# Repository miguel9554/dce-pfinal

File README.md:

# repositorio del proyecto final de dce - 1c2019

integrantes:

- Juan Ciafardini, 97921
- Miguel Perez Andrade, 98599
- Luis Tomás Quiroga, 96337

# 19/12/2019

## 18:00, primera medición

Medimos el punto de operación del amplificador diferencial y la fuente de corriente

* V_R10 [mV]:   571.2
* V_R8  [mV]:   383.8 
* V_R7  [mV]:   5.2
* V_R6  [mV]:   377.7
* V_R2  [mV]:   99
* V_R1  [mV]:   57.3
* V_bQ2 [mV]:   631
* V_bQ3 [mV]:   202.1

Problemas:

* Falta una vía en el emisor de Q2          -> corregido
* Un cacho de tierra no está conectado      -> conecta nada más las resistencias de la etapa de potencia, después lo conectamos
* Se rompio el contacto del capa C3         -> arreglar cuando se mida la señal

## 19:28, segunda medición

Medimos el punto de operación del amplificador diferencial y la fuente de corriente

* V_R10 [mV]:   568.1
* V_R8  [mV]:   380.7 
* V_R7  [mV]:   5.2
* V_R6  [mV]:   374.5
* V_R2  [mV]:   98.1
* V_R1  [mV]:   156.4
* V_bQ2 [mV]:   628
* V_eQ2 [V]:    -9.97
* V_bQ3 [mV]:   200.1
* V_eQ3  [V]:   -9.29

Cálculos

* I_R7  :   0.052u
* I_R6  :   3.74m
* I_R2  :   1.44m
* I_R1  :   2.3m
* I_R15 :   52u
* I_R5  :   16.67u

# 03/02/2020

## 16:40, 1ra medición

Medimos el punto de operación del amplificador diferencial y la fuente de corriente (nodos diff LT)

* V_R10 [mV]:   573.2           (J9 vs V+)
* V_R8  [mV]:   387.5           (J4 vs V+)
* V_R7  [mV]:   5.3         (entre J19 y J2)
* V_R6  [mV]:   378.4           (entre J19 y J20)
* V_R2  [mV]:   99.8            (J3 vs V-)
* V_R1  [mV]:   157.2           (J6 vs V-, entrada)
* V_bQ2 [mV]:   604.7           (J15)
* V_eQ2 [V]:    1.175
* V_bQ3 [mV]:   200.8
* V_eQ3  [V]:   0.806

Soldamos los conectores de Q2 y Q4 que estaban desconectados, medimos de vuelta

## 17:37, 2da medición

Medimos el punto de operación del amplificador diferencial y la fuente de corriente (nodos diff LT)

* V_R10 [mV]:   571.1               (J9 vs V+)
* V_R8  [mV]:   383.5               (J4 vs V+)
* V_R7  [mV]:   190.8               (entre J19 y J2)
* V_R6  [mV]:   191.1               (entre J19 y J20)
* V_R2  [mV]:   130.9               (J3 vs V-)
* V_R1  [mV]:   129.0               (J6 vs V-, entrada)
* V_bQ2 [mV]:   102.3               (J15)
* V_eQ2 [mV]:   696.0
* V_bQ3 [mV]:   103.0
* V_eQ3 [mV]:   696.0

Soldamos R10 a V+, y el capa de filtrado de la fuente de corriente (C7 en Kicad) a V+

## 18:32, 3ra medición

Medimos el punto de operación del amplificador diferencial y la fuente de corriente (nodos diff LT)

* V_R10 [mV]:   563.5               (J9 vs V+)
* V_R8  [mV]:   538.5               (J4 vs V+)
* V_R7  [mV]:   267.4               (entre J19 y J2)
* V_R6  [mV]:   267.3               (entre J19 y J20)
* V_R2  [mV]:   183.0               (J3 vs V-)
* V_R1  [mV]:   180.0               (J6 vs V-, entrada)
* V_bQ2 [mV]:   141.8               (J15)
* V_eQ2 [mV]:   742.0
* V_bQ3 [mV]:   143.2
* V_eQ3 [mV]:   742.0

Cambiamos la resistencia R8 por una de 47, era de 100 y estaba dando mal por eso

## 19:14, 4ta medición

Medimos el punto de operación del amplificador diferencial y la fuente de corriente (nodos diff LT)

* V_R10 [mV]:   561.6               (J9 vs V+)
* V_R8  [mV]:   497.8               (J4 vs V+)
* V_R7  [mV]:   528.9               (entre J19 y J2)
* V_R6  [mV]:   529.4               (entre J19 y J20)
* V_R2  [mV]:   361.8               (J3 vs V-)
* V_R1  [mV]:   357.5               (J6 vs V-, entrada)
* V_bQ2 [mV]:   274.3               (J15)
* V_eQ2 [mV]:   880.0
* V_bQ3 [mV]:   275.5
* V_eQ3 [mV]:   879.0

Medimos con 30V GUARDA CON LAS CHISPAS

## 19:21, 5ta medición

Medimos el punto de operación del amplificador diferencial y la fuente de corriente (nodos diff LT)

* V_R10 [mV]:   582.7               (J9 vs V+)
* V_R8  [mV]:   548.5               (J4 vs V+)
* V_R7  [mV]:   583.3               (entre J19 y J2)
* V_R6  [mV]:   581.7               (entre J19 y J20)
* V_R2  [mV]:   399.1               (J3 vs V-)
* V_R1  [mV]:   392.9               (J6 vs V-, entrada)
* V_bQ2 [mV]:   245.1               (J15)
* V_eQ2 [mV]:   795.0
* V_bQ3 [mV]:   245.7
* V_eQ3 [mV]:   796.0

# 04/02/2020

## 17:42, 1ra medición

Medimos después de soldar el vas sin conectarlo todavía, para ver que todo siga andando

* V_R10 [mV]:   564.2           (J9 vs V+)
* V_R8  [mV]:   497.2           (J4 vs V+)
* V_R7  [mV]:   527.4           (entre J19 y J2)
* V_R6  [mV]:   527.1           (entre J19 y J20)
* V_R2  [mV]:   360.7           (J3 vs V-)
* V_R1  [mV]:   356.0           (J6 vs V-, entrada)
* V_bQ2 [mV]:   274.0           (J15)
* V_eQ2 [mV]:   883.0
* V_bQ3 [mV]:   276.3
* V_eQ3 [mV]:   883.0

## 18:00, 2da medición

Medimos con todo conectado (vas)

* V_R10 [mV]:   32          (J9 vs V+)
* V_R8  [mV]:   58.9            (J4 vs V+)
* V_R7  [mV]:   93.9        (entre J19 y J2)
* V_R6  [mV]:   30.4            (entre J19 y J20)
* V_R2  [mV]:   21.8            (J3 vs V-)
* V_R1  [mV]:   20.3            (J6 vs V-, entrada)
* V_bQ2 [mV]:   7670            (J15)
* V_eQ2 [mV]:   8390
* V_bQ3 [mV]:   7860
* V_eQ3 [mV]:   8460
* V_Vas [mv]:   7980

## 18:26, 3ra medición

Arreglamos la pista que se había cortado (la que iba entre la salida del vas y el diodo) y dimos vuelta los diodos

* V_R10 [mV]:   32          (J9 vs V+)
* V_R8  [mV]:   58.9            (J4 vs V+)
* V_R7  [mV]:   93.9        (entre J19 y J2)
* V_R6  [mV]:   30.4            (entre J19 y J20)
* V_R2  [mV]:   21.8            (J3 vs V-)
* V_R1  [mV]:   20.3            (J6 vs V-, entrada)
* V_bQ2 [mV]:   7670            (J15)
* V_eQ2 [mV]:   8390
* V_bQ3 [mV]:   7860
* V_eQ3 [mV]:   8460
* V_Vas [mv]:   7980

## 19:09, 4ta medición

No estaba conectado el jumper que conectaba la salida del diferencial con el buffer, lo soldamos. También soldamos una pata del transitor del mult de vbe.

* Vcc   [V]:    10   |  30
* V_R10 [mV]:   560.2|580.0             (J9 vs V+)
* V_R8  [mV]:   502.9|567.0             (J4 vs V+)
* V_R7  [mV]:   534.4|602.0             (entre J19 y J2)
* V_R6  [mV]:   536.3|607.5             (entre J19 y J20)
* V_R2  [mV]:   367.1|413.2             (J3 vs V-)
* V_R1  [mV]:   364.9|411.3             (J6 vs V-, entrada)
* V_bQ2 [mV]:   273.6|248.3             (J15)
* V_eQ2 [mV]:   879.0|794.0
* V_bQ3 [mV]:   268.4|237.7
* V_eQ3 [mV]:   875.0|790.0
* V_Vas [mv]:   016.0|019.0

# 06/02/2020

## 17:21, 1ra medición

Alimentación de 27.6 V

* V_R10 [mV]:   590.8           (J9 vs V+)
* V_R8  [mV]:   599.0           (J4 vs V+)
* V_R7  [mV]:   124.3           (entre J19 y J2)
* V_R6  [mV]:   1042.0          (entre J19 y J20)
* V_R2  [mV]:   446.0           (J3 vs V-)
* V_R1  [mV]:   524.0           (J6 vs V-, entrada)
* V_bQ2 [mV]:   15023.0         (J15)
* V_eQ2 [mV]:   24040.0
* V_bQ3 [mV]:   22038.0
* V_eQ3 [mV]:   23075.0

## 18:23, 2da medición

Medición con la realimentación conectada, no está funcionando

* V_R10 [mV]:   603.5           (J9 vs V+)
* V_R8  [mV]:   600.0           (J4 vs V+)
* V_R7  [mV]:   126.2           (entre J19 y J2)
* V_R6  [mV]:   1430.0          (entre J19 y J20)
* V_R2  [mV]:   448.0           (J3 vs V-)
* V_R1  [mV]:   530.0           (J6 vs V-, entrada)
* V_bQ2 [mV]:   15300.0         (J15)
* V_eQ2 [mV]:   24640.0
* V_bQ3 [mV]:   22440.0
* V_eQ3 [mV]:   24000.0

## 18:31, 3ra medición

Medición solo del diferencial

* V_R10 [mV]:   600.8           (J9 vs V+)
* V_R8  [mV]:   558.0           (J4 vs V+)
* V_R7  [mV]:   569.5           (entre J19 y J2)
* V_R6  [mV]:   617.0           (entre J19 y J20)
* V_R2  [mV]:   404.6           (J3 vs V-)
* V_R1  [mV]:   411.0           (J6 vs V-, entrada)
* V_bQ2 [mV]:   332.0           (J15)
* V_eQ2 [mV]:   898.7
* V_bQ3 [mV]:   281.0
* V_eQ3 [mV]:   846.0

# 10/02/2020

# 16:29, 1ra medición

Como no anduvo una mierda la semana pasada, vamos a medir todos los transistores para ver si alguno está roto. Nos basamos en lo explicado en https://www.fluke.com/en-us/learn/best-practices/test-tools-basics/digital-multimeters/how-to-test-diodes-using-a-digital-multimeter y https://electronics.stackexchange.com/a/83752. Los nombres de los transistores van a estar referidos al esquemático de kicad. Todas las mediciones se hacen con un multimetro en modo diodo

* Q3
    * VbeD [mv]: 646
    * VbeI [mv]: 1800
    * VbcD [mv]: 641
    * VbcI [mv]: 0L
    * Vec [mv]: 0L
    * Vce [mv]: 1343
* Q1
    * VbeD [mv]: 649
    * VbeI [mv]: 0L
    * VbcD [mv]: 645
    * VbcI [mv]: 0L
    * Vec [mv]: 700
    * Vce [mv]: 0L
* Q5
    * VbeD [mv]: 642
    * VbeI [mv]: 0L
    * VbcD [mv]: 639
    * VbcI [mv]: 0L
    * Vec [mv]: 0L
    * Vce [mv]: 0L
* Q2
    * VbeD [mv]: 649
    * VbeI [mv]: 0L
    * VbcD [mv]: 648
    * VbcI [mv]: 0L
    * Vec [mv]: 0L
    * Vce [mv]: 1300

* Q2 (tiene cortado base y colector)
    * VbeD [mv]: 600
    * VbeI [mv]: 0L
    * VbcD [mv]: -
    * VbcI [mv]: -
    * Vec [mv]: -
    * Vce [mv]: -

* Q7
    * VbeD [mv]: 656
    * VbeI [mv]: 0L
    * VbcD [mv]: 651
    * VbcI [mv]: 0L
    * Vec [mv]: 710
    * Vce [mv]: 710

* Q10
    * VbeD [mv]: 655
    * VbeI [mv]: 1415
    * VbcD [mv]: 652
    * VbcI [mv]: 0L
    * Vec [mv]: 911
    * Vce [mv]: 0L

* Q8
    * VbeD [mv]: 645
    * VbeI [mv]: 844
    * VbcD [mv]: 640
    * VbcI [mv]: 0L
    * Vec [mv]: 861
    * Vce [mv]: 1715

* Q6
    * VbeD [mv]: 1403
    * VbeI [mv]: 1430
    * VbcD [mv]: 1722
    * VbcI [mv]: 1723
    * Vec [mv]: 700
    * Vce [mv]: 888

* Q9
    * VbeD [mv]: 589
    * VbeI [mv]: 1040
    * VbcD [mv]: 583
    * VbcI [mv]: 1695
    * Vec [mv]: 1008
    * Vce [mv]: 1799

Medimos un mje340 y un mpsa06 buenos, sin usar

* MJE340
    * VbeD [mv]: 618
    * VbeI [mv]: 0L
    * VbcD [mv]: 613
    * VbcI [mv]: 0L
    * Vec [mv]: 0L
    * Vce [mv]: 0L

* MPSA06
    * VbeD [mv]: 668
    * VbeI [mv]: 0L
    * VbcD [mv]: 665
    * VbcI [mv]: 0L
    * Vec [mv]: 0L
    * Vce [mv]: 0L

Con estás ultimas mediciones, parece que están todos rotos salvo Q5. Es posible que el circuito externo que tiene cada dispositivo esté alterando las mediciones, y los resultados no sean correctos. Vamos a sacar los transistores y medirlos solos para comprobar.

Mediciones con los transistores desoldados:

* Q9
    * VbeD [mv]: 624
    * VbeI [mv]: 0L
    * VbcD [mv]: 620
    * VbcI [mv]: 0L
    * Vec [mv]: 0L
    * Vce [mv]: 0L

* Q3
    * VbeD [mv]: 646
    * VbeI [mv]: 0L
    * VbcD [mv]: 643
    * VbcI [mv]: 0L
    * Vec [mv]: 0L
    * Vce [mv]: 0L

* Q10
    * VbeD [mv]: 661
    * VbeI [mv]: 0L
    * VbcD [mv]: 630
    * VbcI [mv]: 0L
    * Vec [mv]: 0L
    * Vce [mv]: 0L

* Q7 (parece estar cagado, ver la potencia)
    * VbeD [mv]: 653
    * VbeI [mv]: 0L
    * VbcD [mv]: 650
    * VbcI [mv]: 0L
    * Vec [mv]: \~710
    * Vce [mv]: \~710

Con Q9 comprobamos la medición volviendo a soldarlo, y dio mal igual que antes. Esto nos da la pauta de que el circuito externo a cada dispositivo esta perturbando la medición cuando medimos al dispositivo conectado al resto del circuito.

Q7 parece estar cagado, la medición del transistor solo da mal (no hay abierto entre colector y emisor). En base a esto y a que el circuito diferencial estaba funcionando sin la etapa VAS, suponemos que cambiar este transistor va a solucionar el problema.

## 18:52, 2da medición

Medimos con Q7 reemplazado, el circuito diferencial con el vas (medimos rápidamente la fuente de corriente y el diferencial antes de esto y daba bien)
Se quemó la resistencia R4 (en PCB)

* V_R10 [mV]:   573.3           (J9 vs V+)
* V_R8  [mV]:   536.6           (J4 vs V+)
* V_R7  [mV]:   081.5           (entre J19 y J2)
* V_R6  [mV]:   1018.0           (entre J19 y J20)
* V_R2  [mV]:   384.0           (J3 vs V-)
* V_R1  [mV]:   430.5           (J6 vs V-, entrada)
* V_bQ2 [mV]:   -15150          (J15)
* V_eQ2 [mV]:   -18160
* V_bQ3 [mV]:   -14260
* V_eQ3 [mV]:   -19320
* V_oVAS[mV]:   -18750

## 19:07, 2da medición

Medimos solo el diferencial para comprobar que siga andando

* V_R10 [mV]:   599.0           (J9 vs V+)
* V_R8  [mV]:   541.9           (J4 vs V+)
* V_R7  [mV]:   530.8           (entre J19 y J2)
* V_R6  [mV]:   577.9           (entre J19 y J20)
* V_R2  [mV]:   373.6           (J3 vs V-)
* V_R1  [mV]:   378.4           (J6 vs V-, entrada)
* V_bQ2 [mV]:   319.7          (J15)
* V_eQ2 [mV]:   886.6
* V_bQ3 [mV]:   270.4
* V_eQ3 [mV]:   843.4

Vamos a medir los transistores del par diferencial y su carga activa

* Q1
    * VbeD [mv]: 647
    * VbeI [mv]: 0L
    * VbcD [mv]: 643.8
    * VbcI [mv]: 0L
    * Vec [mv]: 0L
    * Vce [mv]: 0L

* Q5
    * VbeD [mv]: 640.0
    * VbeI [mv]: 0L
    * VbcD [mv]: 643.4
    * VbcI [mv]: 0L
    * Vec [mv]: 0L
    * Vce [mv]: 0L

* Q2
    * VbeD [mv]: 668.0
    * VbeI [mv]: 0L
    * VbcD [mv]: 599.5
    * VbcI [mv]: 0L
    * Vec [mv]: 0L
    * Vce [mv]: 0L

* Q4
    * VbeD [mv]: 600.0
    * VbeI [mv]: 0L
    * VbcD [mv]: 666.0
    * VbcI [mv]: 0L
    * Vec [mv]: 0L
    * Vce [mv]: 0L

* Q6
    * VbeD [mv]: 582.5
    * VbeI [mv]: 0L
    * VbcD [mv]: 643.5
    * VbcI [mv]: 0L
    * Vec [mv]: 0L
    * Vce [mv]: 0L

* Q8
    * VbeD [mv]: 642.5
    * VbeI [mv]: 0L
    * VbcD [mv]: 640.0
    * VbcI [mv]: 0L
    * Vec [mv]: 0L
    * Vce [mv]: 0L

##  20:06, 3ra medición

Probamos todos los transistores y parecen estar bien. Soldamos la pistas de la base de Q2 y el colector Q6 (fuente de corriente) que no estaban unidas. Medimos de vuelta

* V_R10 [mV]:   571.5           (J9 vs V+)
* V_R8  [mV]:   558           (J4 vs V+)
* V_R7  [mV]:   85.8           (entre J19 y J2)
* V_R6  [mV]:   10892           (entre J19 y J20)
* V_R2  [mV]:   411.4           (J3 vs V-)
* V_R1  [mV]:   460           (J6 vs V-, entrada)
* V_bQ2 [mV]:   -1513          (J15)
* V_eQ2 [mV]:   -18.33
* V_bQ3 [mV]:   -14092
* V_eQ3 [mV]:   -19.53
* V_oVAS[mV]:   -18507

Las fuentes daban 30 mili cada una
Medimos el diferencial primero y estaba balanceado

#   11/02/2020

##  18:16, 1ra medición

Medición sin realizar ningún cambio.

* V_R10 [mV]:   603.4           (J9 vs V+)
* V_R8  [mV]:   564.0           (J4 vs V+)
* V_R7  [mV]:   576.7           (entre J19 y J2)
* V_R6  [mV]:   581.8           (entre J19 y J20)
* V_R2  [mV]:   395.5           (J3 vs V-)
* V_R1  [mV]:   393.8           (J6 vs V-, entrada)
* V_bQ2 [mV]:   359.7          (J15)
* V_eQ2 [mV]:   938.0
* V_bQ3 [mV]:   359.2
* V_eQ3 [mV]:   932.0
* V_oVAS[mV]:   075.4

El problema era el potenciómetro del multiplicador de vbe que estaba flojo.

##  Modificaciones
* Sacamos el capacitor de 1uF entre -VCC y GND porque estaba cortada la pista de -VCC en ese nodo.
* Cambiamos el potenciómetro, pareciera seguir habiendo algún problema relacionado a su conexión.

# 13/02/2020

Empezamos viendo si el pote está bien soldado, si hay la resistencia que tiene que haber entre las pistas. Lo resoldamos y parece dar bien

##  16:55, 1ra medición

Medición después de soldar bien el pote.

* V_R10 [mV]:   605.7           (J9 vs V+)
* V_R8  [mV]:   569.1           (J4 vs V+)
* V_R7  [mV]:   580.5           (entre J19 y J2)
* V_R6  [mV]:   585.9           (entre J19 y J20)
* V_R2  [mV]:   397.3           (J3 vs V-)
* V_R1  [mV]:   396.0           (J6 vs V-, entrada)
* V_bQ2 [mV]:   367.4          (J15)
* V_eQ2 [mV]:   946.0
* V_bQ3 [mV]:   365.9
* V_eQ3 [mV]:   941.0
* V_oVAS[mV]:   57.0

Da bien! Parece ser que el problema era el pote.

Ahora vamos a medir la ganancia con fin=1k.
Vpp entrada [mV]    Vpp salida [V]  Ganancia
200     5.4     27
300     8.48    28.26
400     11.12   27.8
500     13.8    27.6
600     16.20   27
800     21.2    26.5
1000    26.40   26.4
1200    31.8    26.5
1500    39.20   26.13
1530    40      26.14

Ahora vamos a medir la ganancia con fin=10k (hay que recalcular la ganancia).
Vpp entrada [mV]    Vpp salida [V]  Ganancia
200     5.12    27
300     8.48    28.26
400     11.04   27.8
500     13.44   27.6
600     16.00   27
800     21.2    26.5
1000    26.40   26.4
1200    31.8    26.5
1500    40      26.13
1530    40      26.14

Medimos la salida con 1 Vpp a la entrada, y variando la frecuencia.
f [Hz]  Vpp salida [V]
20  26.8
200 26.8
2k  26.6
20k 26.8
50k 26.8
200k    26

Da joya la baja potencia, arrancamos a soldar la parte de potencia.

Cosas que hay que comprar:
* Disipadores
* Pasta térmica
* Diodos 1N4148
* Capacitores de 1u y 50V
* Resistencia de 50W

Cosas para ver:
* Ver porque que en el esquemático hay 1N4148 cuando debería haber LM385
* Soldar todas las pistas de los componentes de potencia cuando 
* Cambiar C7 que está quemado, y volver a poner C8

# 17/02/2020

La idea de hoy era soldar toda la etapa de potencia y montar los disipadores. El disipador de los transistores de potencia y el multiplicador de vbe no se pudo montar, asi que solo soldamos la etapa de potencia. Medimos continuidad y parece estar todo bien conectado. Solo falta soldar las pistas de arriba de los transistores que van al disipador. No lo hicimos para que tengan mas movilidad cuando pongamos el disipador. Mañana hay que comprar
* Disipador ZD27-10, de 10 cm de largo
* Tornillos y mica

# 21/02/2020

Ya está todo soldado y armado, vamos a medir la polarización para todo el circuito

## 1ra medición, 18:26

* V_R10 [mV]:   603
* V_R8  [mV]:   572
* V_R7  [mV]:   579.5
* V_R6  [mV]:   581.7
* V_R2  [mV]:
* V_R1  [mV]:
* V_bQ2 [mV]:
* V_eQ2 [mV]:
* V_bQ3 [mV]:
* V_eQ3 [mV]:
* V_oVAS[mV]:
* V_bQ11[mV]:
* V_bQ16[mV]:
* V_bQ12[mV]:
* V_bQ15[mV]:
* V_R18 [mV]:
* V_R19 [mV]:

Tratabamos de medir y cuando mediamos algunos nodos (VoVas, VR7, VR6) la fuente empezaba a entregar corrientes erróneas. Vamos a medir con un osciloscopio enganchado en VoVas para ver si hay oscilaciones

Encontramos una oscilación, chequeamos en la simulación y encontramos que con el capa de compensación de 100p, el circuito está inestable. Lo reemplazamos por uno de 470p que da estable. REEMPLAZAR EN EL LTSPICE EL CAPA DE 100P POR ESTE DE 470P

Hablamos con Fede
- Tratar de que haya aprox 100 mA en la rama de salida, ahora hay 500mA. Probamos llevando la resistencia del mult de vbe 1.5K, daba bien la THD y aprox 100 mA a la salida, ver si cambiamos el pote por uno de 500.
- SIEMPRE limitar la corriente de las fuentes antes de medir. Para esto, llevar a cero la tensión y el límite de corriente, cortocircuitar la fuente e incrementar el límite de corriente hasta llegar a la limitación deseada.

Cosas para cambiar en las simulaciones
- Poner un capacitor de 470p
- Ver la resistencia del mult de vbe, en 1.5k aparentemente da bien

## 2da medición, 19:58

Medimos después de reemmplazar el capa de 100p por uno de 470p

* V_R10 [mV]:   610
* V_R8  [mV]:   567
* V_R7  [mV]:   577
* V_R6  [mV]:   584
* V_R2  [mV]:   397.4
* V_R1  [mV]:   396.9
* V_bQ2 [mV]:   370.2
* V_eQ2 [mV]:   954
* V_bQ3 [mV]:   369.2
* V_eQ3 [mV]:   948
* V_oVAS[mV]:   -1914

# 28/02/20

Vamos a medir la polarización de la etapa de potencia

## 1ra medición, 19:54

Medimos 

* V_R10 [mV]: 599 
* V_R8  [mV]: 568
* V_R7  [mV]: 539
* V_R6  [mV]: 583
* V_R2  [mV]: 396
* V_R1  [mV]: 394
* V_bQ2 [mV]: 356
* V_eQ2 [mV]: 930
* V_bQ3 [mV]: 356
* V_eQ3 [mV]: 926
* V_oVAS[mV]: -1800
* V_bQ11[mV]: 1060
* V_bQ16[mV]: 984
* V_R20 [mV]: 848
* V_R18 [mV]: 0
* V_R19 [mV]: 0
* V_o   [mV]: 57

## 2da medición, 20:25

Soldamos el pin de alimentación de V+, estaba desconectado. Medimos y NO DABA, no medimos todos los nodos por paja

* V_R10 [mV]: 
* V_R8  [mV]: 
* V_R7  [mV]: 
* V_R6  [mV]: 583
* V_R2  [mV]: 396
* V_R1  [mV]: 394
* V_bQ2 [mV]: 356
* V_eQ2 [mV]: 930
* V_bQ3 [mV]: 356
* V_eQ3 [mV]: 926
* V_oVAS[mV]: -1800
* V_bQ11[mV]: 1060
* V_bQ16[mV]: 984
* V_R20 [mV]: 848
* V_R18 [mV]: 0
* V_R19 [mV]: 
* V_o   [mV]: 56

## 3ra medición, 20:50

Soldamos bien el colector de Q17 que no estaba haciendo contacto con la pista. NO DIO

## 4ta medición, 21:08

Soldamos bien el emisor de Q18 que no estaba haciendo contacto con la resistencia R22.

driver arriba
23.96
24.4

driver abajo
24.03
24.4

transistor exterior arriba
9.99
10.2

Vimos que llevando el pote a 0, teníamos 0.05mV sobre las resistencias de emisor, y si lo tirabamos a 200, había 0V. Hay que bajar la resistencia.

# 02/03/202

Modificamos la resistencia del multiplicador de vbe a 1.2 k más el preset. Procedemos a medir la polarización.

# Primera medición, 14:55

Sin conectar las fuentes internas

* V_R10 [mV]: 612             (J9 vs V+)
* V_R8  [mV]: 572             (J4 vs V+)
* V_R7  [mV]: 587             (entre J19 y J2)
* V_R6  [mV]: 589             (entre J19 y J20)
* V_R2  [mV]: 403             (J3 vs V-)
* V_R1  [mV]: 402             (J6 vs V-, entrada)
* V_bQ2 [mV]: 361            (J15)
* V_eQ2 [mV]: 938  
* V_bQ3 [mV]: 360  
* V_eQ3 [mV]: 934  
* V_oVAS[mV]: -1980
* V_bQ11[mV]: 
* V_bQ16[mV]: 
* V_R20 [mV]: 
* V_R18 [mV]: 
* V_R19 [mV]: 
* V_o   [mV]: 57

Corriente de las fuentes entre 40 y 50 mA.

# Segunda medición, 15:30

Conectadas las fuentes internas

* V_R10 [mV]: 601             (J9 vs V+)
* V_R8  [mV]: 576             (J4 vs V+)
* V_R7  [mV]: 584             (entre J19 y J2)
* V_R6  [mV]: 588             (entre J19 y J5)
* V_R2  [mV]: 400             (J3 vs V-)
* V_R1  [mV]: 398             (J6 vs V-, entrada)
* V_bQ2 [mV]: 354            (J15)
* V_eQ2 [mV]: 926  
* V_bQ3 [mV]: 352  
* V_eQ3 [mV]: 923  
* V_oVAS[mV]: -2000
* V_bQ11[mV]: 1192
* V_bQ16[mV]: 1295
* V_R20 [mV]: 1278
* V_R18 [mV]: 5				(50 mA)
* V_R19 [mV]: 5
* V_o   [mV]: 55

# Tercera medición, 15:56

Cambiamos la resistencia del preset de 40 ohm a 120 ohm para bajar la corrien te en la rama de salida.

* V_R10 [mV]: 605
* V_R8  [mV]: 574
* V_R7  [mV]: 585
* V_R6  [mV]: 590
* V_R2  [mV]: 401
* V_R1  [mV]: 399
* V_bQ2 [mV]: 356
* V_eQ2 [mV]: 931 
* V_bQ3 [mV]: 356  
* V_eQ3 [mV]: 926
* V_oVAS[mV]: -1970
* V_bQ11[mV]: 1249
* V_bQ16[mV]: 1140
* V_R20 [mV]: 1278
* V_R18 [mV]: 0.92				(9.2 mA)
* V_R19 [mV]: 0.92
* V_o   [mV]: 52

# Cuarta medición, 17:13

Se produjo un corto al medir señal.

* V_R10 [mV]: 608
* V_R8  [mV]: 573
* V_R7  [mV]: 585
* V_R6  [mV]: 590
* V_R2  [mV]: 401
* V_R1  [mV]: 399
* V_bQ2 [mV]: 362
* V_eQ2 [mV]: 946 
* V_bQ3 [mV]: 362  
* V_eQ3 [mV]: 940
* V_oVAS[mV]: -1950
* V_bQ11[mV]: 1290
* V_bQ16[mV]: 1129
* V_R20 [mV]: 1190
* V_R18 [mV]: 0.27				(2.5 mA)
* V_R19 [mV]: 0.25
* V_o   [mV]: 54

Bajó la corriente de salida. Probablemente se corrió el potenciómetro.
Se solucionó acomodando algunos contactos de las fuentes de alimentación.

El circuito presenta una senoidal de 7.6 MHz y 1.2 Vpp a la salida en ausencia
de señal de entrada. Al agregarse la señal de entrada se suma a la salida con poca amplificación.
Probar cambiar capacitor de compensación.

# 03/03/202

Soldamos dos capacitores de 220 pF entre base y colector de los transistores externos del driver.

# Primera medición, 16:23

* V_R10 [mV]: 604
* V_R8  [mV]: 570
* V_R7  [mV]: 581
* V_R6  [mV]: 587
* V_R2  [mV]: 399
* V_R1  [mV]: 397
* V_bQ2 [mV]: 355
* V_eQ2 [mV]: 932  
* V_bQ3 [mV]: 353 
* V_eQ3 [mV]: 928  
* V_oVAS[mV]: -1980
* V_bQ11[mV]: 1249
* V_bQ16[mV]: 1146
* V_R20 [mV]: 1190
* V_R18 [mV]: 0.90		(9 mA)
* V_R19 [mV]: 0.93
* V_o   [mV]: 48

La ganancia está muy afectada para casi todas las frecuencias, ya en la salida del VAS.
La mayor ganancia encontrada es 3, para 1 MHz.
La cuadrada muestra que no està sobrecompensado.

# 05/03/2020

Medimos primero sin cambiar nada

* V_R10 [mV]: 601
* V_R8  [mV]: 574
* V_R7  [mV]: 584
* V_R6  [mV]: 587
* V_R2  [mV]: 400
* V_R1  [mV]: 399
* V_bQ2 [mV]: 350
* V_eQ2 [mV]: 924  
* V_bQ3 [mV]: 350 
* V_eQ3 [mV]: 919  
* V_oVAS[mV]: -1936
* V_bQ11[mV]: 1277
* V_bQ16[mV]: 1104
* V_R20 [mV]: 1177
* V_R18 [mV]: 0.80      (8 mA)
* V_R19 [mV]: 0.90
* V_o   [mV]: 48

Medimos para verificar que esté igual que al inicio

* V_R10 [mV]: 600
* V_R8  [mV]: 571
* V_R7  [mV]: 582
* V_R6  [mV]: 587
* V_R2  [mV]: 398
* V_R1  [mV]: 397
* V_bQ2 [mV]: 345
* V_eQ2 [mV]: 919  
* V_bQ3 [mV]: 346 
* V_eQ3 [mV]: 913  
* V_oVAS[mV]: -1968
* V_bQ11[mV]: 1241
* V_bQ16[mV]: 1137
* V_R20 [mV]: 1181
* V_R18 [mV]: 1.80      (18 mA)
* V_R19 [mV]: 1.70
* V_o   [mV]: 45

Si se toca con metal Vin, Vout, R18 o R19, VbQ2: aparece la oscilación de 7 Mhz 2 Vpp a la salida.
Si se toca VbQ3: la tensión aumenta indefinidamente en amplitud (a veces).

# 06/03/2020

Medimos después de agergar un capa de 220 pF en paralelo con el que ya pusimos en Q12

* V_R10 [mV]: 602
* V_R8  [mV]: 573
* V_R7  [mV]: 584
* V_R6  [mV]: 587
* V_R2  [mV]: 399
* V_R1  [mV]: 397
* V_bQ2 [mV]: 366
* V_eQ2 [mV]: 957  
* V_bQ3 [mV]: 362 
* V_eQ3 [mV]: 953  
* V_oVAS[mV]: -1987
* V_bQ11[mV]: 1243
* V_bQ16[mV]: -1151
* V_R20 [mV]: 1185
* V_R18 [mV]: 0.8      (8 mA)
* V_R19 [mV]: 0.8
* V_o   [mV]: 43

Arreglamos el capa de 1000 uF que estaba mal soldado. El problema era que como no hacía contacto, teníamos realimentación unitaria.

Le soldamos a cada driver un capacitor extra en paralelo. Quedó cada uno con dos capas de 220 pF.

La frecuencia de corte inferior estaba en aproximadamente 25 Hz.

La ganancia estaba dando aprox 20. Para frecuencias mas altas se va a 25.

# 09/03/2020

Capacitor 440 pF en el driver clase C del semiciclo negativo, desconectado en el positivo.
Soldamos el segundo capacitor de filtrado de fuente (para -VCC) de 1000 uF.
Sin carga.

## Resultados 17:34
* Ruido de 50 Hz 280 mVpp
* Con las fuentes apagadas, pero conectadas, el mismo ruido prevalece con amplitud 50 mVpp

## Medición ancho de banda (entrada 100 mVpp) 18:00
* Frec      Amplitud    G
* 1 kHz:    2.70 Vpp    27
* 10 kHz:   2.64 Vpp    26.4
* 20 kHz:   2.68 Vpp    26.8
* 50 kHz:   2.46 Vpp    24.6
* 100 kHz:  2.1 Vpp     21
* 150 kHz:  1.82 Vpp    18.2
* 200 kHz:  1.58 Vpp    15.8

## Medición ancho de banda (entrada 1 Vpp) 18:05
* Frec      Amplitud    G
* 1 kHz:    26.4 Vpp    26.4
* 10 kHz:   27.0 Vpp    27.0    (sube la corriente entragada por la fuente a 80 mA)
* 100 kHz:  21.2 Vpp    21.2

Soldamos el capacitor de 440 pF en el driver clase C del semiciclo positivo.

* La amplificación sigue igual. El ruido en el semiciclo positivo parece venir de la conmutación
porque aparece al superar los 10 V.
* A partir de 1.2 Vpp de entrada satura el semicilo negativo (imagen enviada por mail).

## Medición con carga (entrada 1 kHz) 18:42
* Vin           Vout        G
* 46 mVpp:      632 mVpp    13.7
* 54 mVpp:      920 mVpp    17.0
* 100 mVpp:     A partir de esta tensión aparece un ruido en el cruce por cer
en la entrada y se amplifica a la salida.

Había un problema de masas, conectamos bien la masa del osciloscopio y empezamos a medir bien.

## Medición con carga (entrada 1 kHz) 19:18
* Vin           Vout        G
* 100 mVpp     2.54 Vpp    25.4
* 120 mVpp     3.24        27
* 140 mVpp     3.24        23.1
* 160 mVpp     4           25
* 200 mVpp     5.8         28

A partir de 140 mV, la señal empieza a moverse en el osciloscopio, y no es por ruido de linea. Posiblemente sea por el trigger, probar con el trigger externo conectado a la otra salida del generador de señales.

Recapitulando lo de hoy,

* Cuando la señal llega tiene 10 Vpico (el umbral de conmutación), aparece mucho ruido en el maximo del ciclo positivo
* Cuando empieza a crecer mas la señal, el ruido del ciclo positivo se achica, pero aparece una especie de rectificacion en el ciclo negativo
* Probamos con carga, y la corriente de las fuentes interiores crecía mucho más que la de las exteriores.

# 10/03/2020

Encontramos errores en la continua y volvimos a medir.

* V_R10 [mV]: 79
* V_R8  [mV]: 79
* V_R7  [mV]: 198
* V_R6  [mV]: 0
* V_R2  [mV]: 0
* V_R1  [mV]: 0
* V_bQ2 [mV]: -23000
* V_eQ2 [mV]: -24500
* V_bQ3 [mV]: -23830
* V_eQ3 [mV]: -24700
* V_oVAS[mV]: -24000
* V_bQ11[mV]: 
* V_bQ16[mV]: 
* V_R20 [mV]: 
* V_R18 [mV]: 
* V_R19 [mV]: 
* V_o   [mV]: 

Solo diferencial

* V_R10 [mV]: 600
* V_R8  [mV]: 59
* V_R7  [mV]: 199
* V_R6  [mV]: 0
* V_R2  [mV]: 0
* V_R1  [mV]: 0
* V_bQ2 [mV]: -24000
* V_bQ3 [mV]: -24000

LLegamos y medimos la ganancia. 

* V_R8  [mV]: 108
* V_R7  [mV]: 199.6
* V_R6  [mV]: 1
* V_R15 [mV]: 23850
* V_R4  [mV]: 1.7
* V_R2  [mV]: 0.7
* V_R1  [mV]: 0.8

# 12/03/2020

Unimos los planos de tierra con cables porque sospechamos que el error está en las conexiones de tierra.

Encontramos que cuando prendemos con la carga conectada solo con las fuentes exteriores, hay un transitorio de aproximadamente 5 segundos en el que la fuente positiva corta por corriente. Si es con las fuentes interiores, dura menos.

## Medición de señal sin carga (f = 1 kHz) 19:34

* Vin [mV]   Vout [V]
* 112        2.66
* 208        5.28
* 300        7.88
* 530        13.8
* 800        21.4
* 1020       26.8
* 1260       32.4
* 1460       38.0
* 1600       42.8
* 1700       45.2

# 13/03/2020

* Reemplazamos el capa de filtrado de la fuente (entre -Vcc y gnd) de 100 uF por otro de 1 uF y sigue habiendo un transitorio de aprox 3 segs. La polarización da bien.

* Vamos a mandar señal a ver si sigue amplificando bien como ayer. Dio OK

* Ahora, con las fuentes exteriores en 30 V (máxima excursión 60 V), vamos a ver hasta que amplitud de salida podemos trabajar sin distorsión (sin carga).

* Llegamos hasta una entrada de 2,16 Vpp con una salida de 50,8 Vpp. A partir de esto, empieza a haber distorsión.

* Tabla de tensiones y potencias

* Vinpp [V] Vopp [V]    Prms [W]
* 0,2       5           0,4
* 0,32      8           1
* 0,72      17,88       5
* 1         25          10
* 1,24      31          15
* 2         50.59       40
* 2,26      56.57       50

Mediciones
Vinpp [mV] Vo [V]
208 5,16
308 7,68
332 8,32
400 10,2
524 13,3
624 16,2
720 18,2

Llegamos hasta estos últimos valores, después la señal de salida empezaba a distorsionarse. Recortaba en el cilco positivo en 9,2 V, y en el negativo podía seguir creciendo pero deformada.

ERROR:

Encontramos que el diodo D3 (nomenclatura kicad) estaba conectado al emisor de Q8 en lugar del colector. Lo corregimos cortando la pista y uniendo con un cable. El kicad quedó actualizado.

Ya lo arreglamos, medimos

Mediciones
Vinpp [mV] Vo [V]
216 5,20
312 7,76
528 13,1

Estaba recortando en 6 V, desconectamos y reconectarmos la fuente y anduvo

Vinpp [mV] Vo
528 13,4
624 16,2
720 18,2

En 650 empieza a distorsionar el pico negativo empieza a distorsionarse. A partir de 750, Vcc+ deja de entregar y corriente y el ciclo positivo recorta en 9,2

Tratamos de poner 15 V en las fuentes interiores, pero las corrientes divergen, teníamos que apagarlo en alrededor de 170 mA.

Con 12 V no divergia, empezamos a subir las fuentes y hasta 14 V parecía andar bien.

Los zeners están al revés en el Douglas-Self, y en el Kicad estaban como en el Douglas Self y los dimos vuelta. Ver como van

# 16/03/2020

Hoy llegamos y tratamos de llegar a la máxima excursión de la vez pasada sin carga. Nos encontramos que a partir de aproximadamente 16 Vpp a la salida la corriente que entregaban las fuentes interiores subia demasiado, hasta 300 mA.
Empezamos a revisar y encontramos que el diodo D4 (de LTSpice) estaba al revés, lo dimos vuelta y se arreglo. Amplificamos sin carga, y llegamos a una máxima excursión de 50 Vpp, igual que la vez pasada.
Después de esto, amplificamos con carga y la parte positiva conmutaba sin problemas. La parte negativa conmuta un poco más lento, y parece tener más distorsión. Hay que medir las caidas de tensión en los caminos de Vo y los emisores de los transistores clase C hasta las  bases de los drivers de los clases C, y verificar que haya simetría. Probablemente este conmutando más tarde la etapa negativa por algo que está desbalanceado.
Llegamos a amplificar hasta 35 Vpp a la salida.

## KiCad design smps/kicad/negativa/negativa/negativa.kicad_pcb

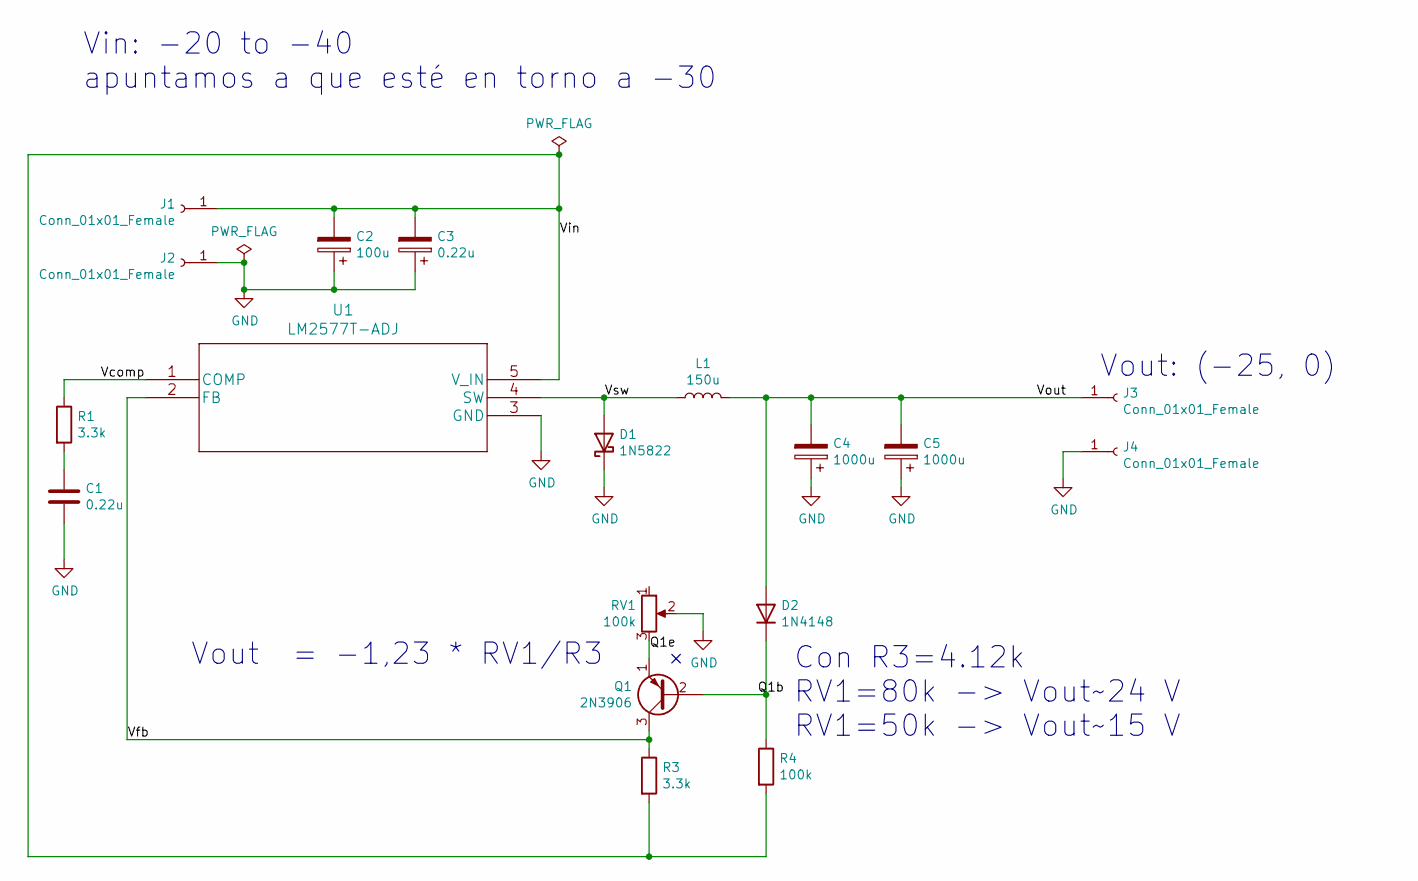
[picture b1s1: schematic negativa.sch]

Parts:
C1, C3: 0.22u; C_1206_3216Metric_Pad1.33x1.80mm_HandSolder
C2: 100u; CP_Radial_D8.0mm_P3.50mm
C4, C5: 1000u; CP_Radial_D16.0mm_P7.50mm
D1: 1N5822; D_DO-201AD_P15.24mm_Horizontal
D2: 1N4148; D_DO-35_SOD27_P7.62mm_Horizontal
J1, J2, J3, J4: Conn_01x01_Female; Banana_Jack_1Pin
L1: 150u; L_Toroid_Vertical_L31.8mm_W15.9mm_P13.50mm_Bourns_5700
Q1: 2N3906; TO-92_Inline
R1, R3: 3.3k; R_1206_3216Metric_Pad1.30x1.75mm_HandSolder
R4: 100k; R_1206_3216Metric_Pad1.30x1.75mm_HandSolder
RV1: 100k; Potentiometer_Bourns_3296W_Vertical
U1: LM2577T-ADJ

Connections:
/Q1b: D2.1 (K), Q1.2 (B), R4.1
/Q1e: Q1.1 (E), RV1.3
/Vcomp: R1.1, U1.1 (COMP)
/Vfb: Q1.3 (C), R3.1, U1.2 (FB)
/Vin: C2.2, C3.2, J1.1, R3.2, R4.2, U1.5 (V_IN)
/Vout: C4.2, C5.2, D2.2 (A), J3.1, L1.2
/Vsw: D1.2 (A), L1.1, U1.4 (SW)
GND: C1.2, C2.1, C3.1, C4.1, C5.1, D1.1 (K), J2.1, J4.1, RV1.2, U1.3 (GND)
unnamed: C1.1, R1.2

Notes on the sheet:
Vin: -20 to -40 apuntamos a que esté en torno a -30
Vout: (-25, 0)
Vout = -1,23 * RV1/R3
Con R3=4.12k RV1=80k -> Vout~~24 V RV1=50k -> Vout~~15 V

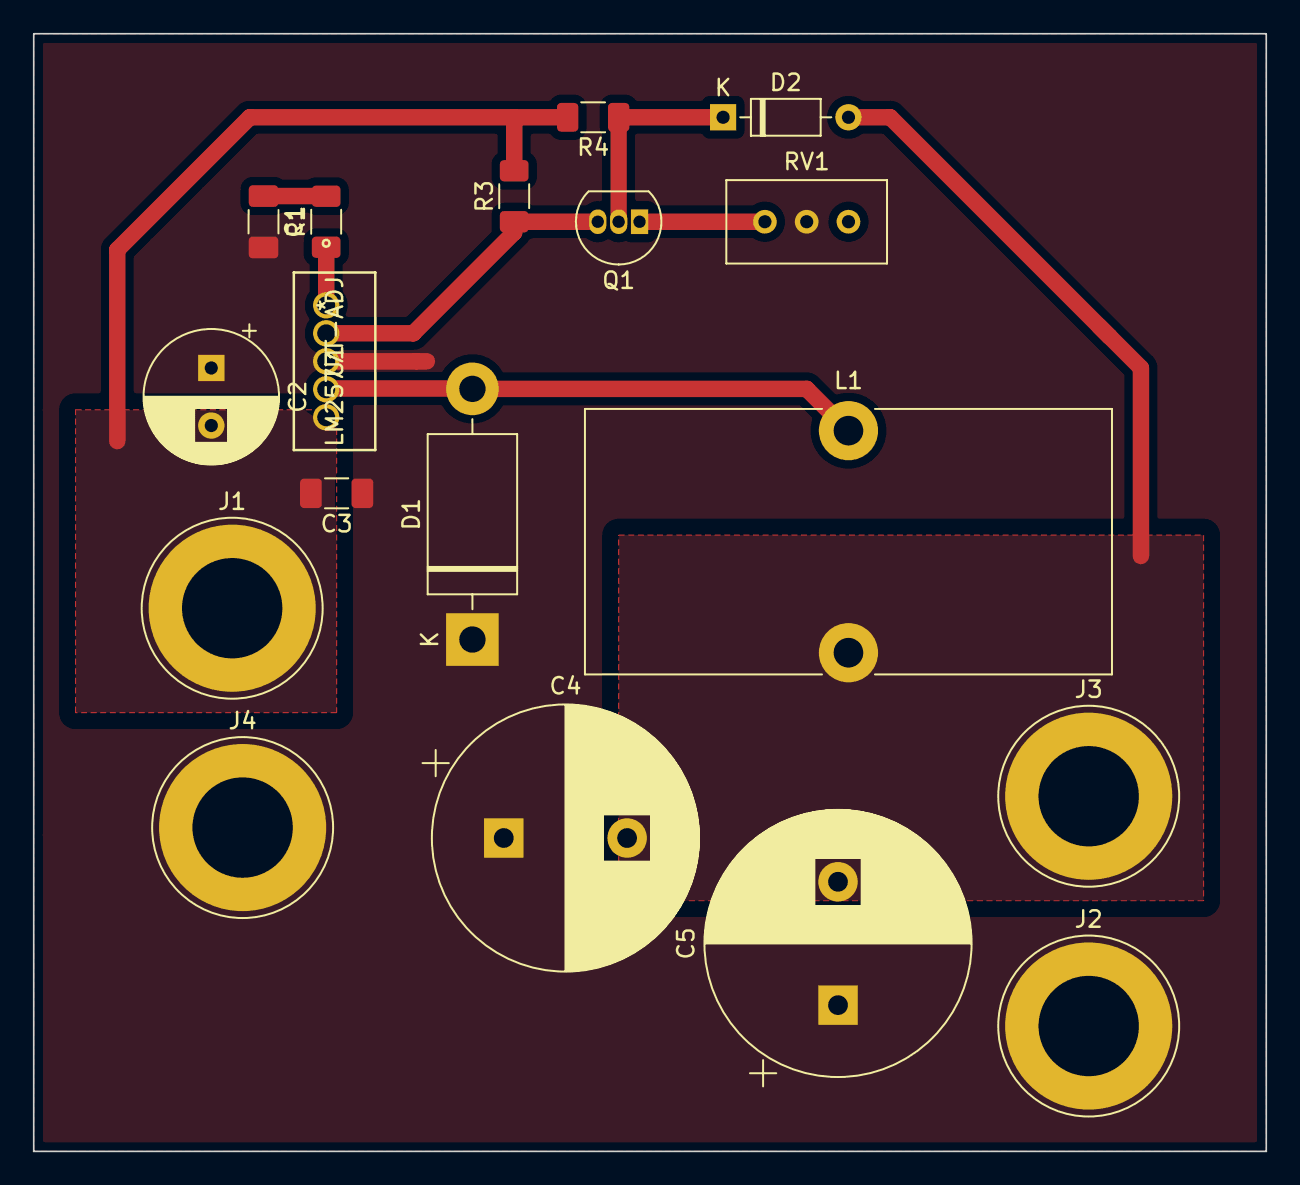
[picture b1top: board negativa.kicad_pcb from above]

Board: 2 copper layers, 74.9 x 67.9 mm, 18 parts (0 on the bottom side), 9 nets.

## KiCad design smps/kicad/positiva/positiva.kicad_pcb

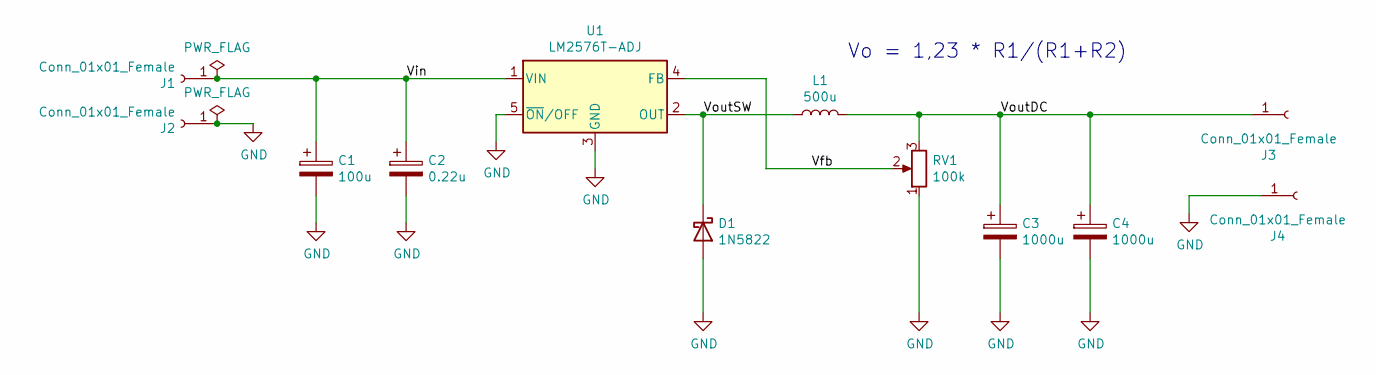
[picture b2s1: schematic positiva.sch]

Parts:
C1: 100u; CP_Radial_D8.0mm_P3.50mm
C2: 0.22u; C_1206_3216Metric_Pad1.33x1.80mm_HandSolder
C3, C4: 1000u; CP_Radial_D16.0mm_P7.50mm
D1: 1N5822; D_DO-201AD_P15.24mm_Horizontal
J1, J2, J3, J4: Conn_01x01_Female; Banana_Jack_1Pin
L1: 500u; L_Toroid_Vertical_L31.8mm_W15.9mm_P13.50mm_Bourns_5700
RV1: 100k; Potentiometer_Bourns_3296W_Vertical
U1: LM2576T-ADJ; TO-220-5_Vertical

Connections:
/Vfb: RV1.2, U1.4 (FB)
/Vin: C1.1, C2.1, J1.1, U1.1 (VIN)
/VoutDC: C3.1, C4.1, J3.1, L1.2, RV1.3
/VoutSW: D1.1 (K), L1.1, U1.2 (OUT)
GND: C1.2, C2.2, C3.2, C4.2, D1.2 (A), J2.1, J4.1, RV1.1, U1.3 (GND), U1.5 (~ON~/OFF)

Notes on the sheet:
Vo = 1,23 * R1/(R1+R2)

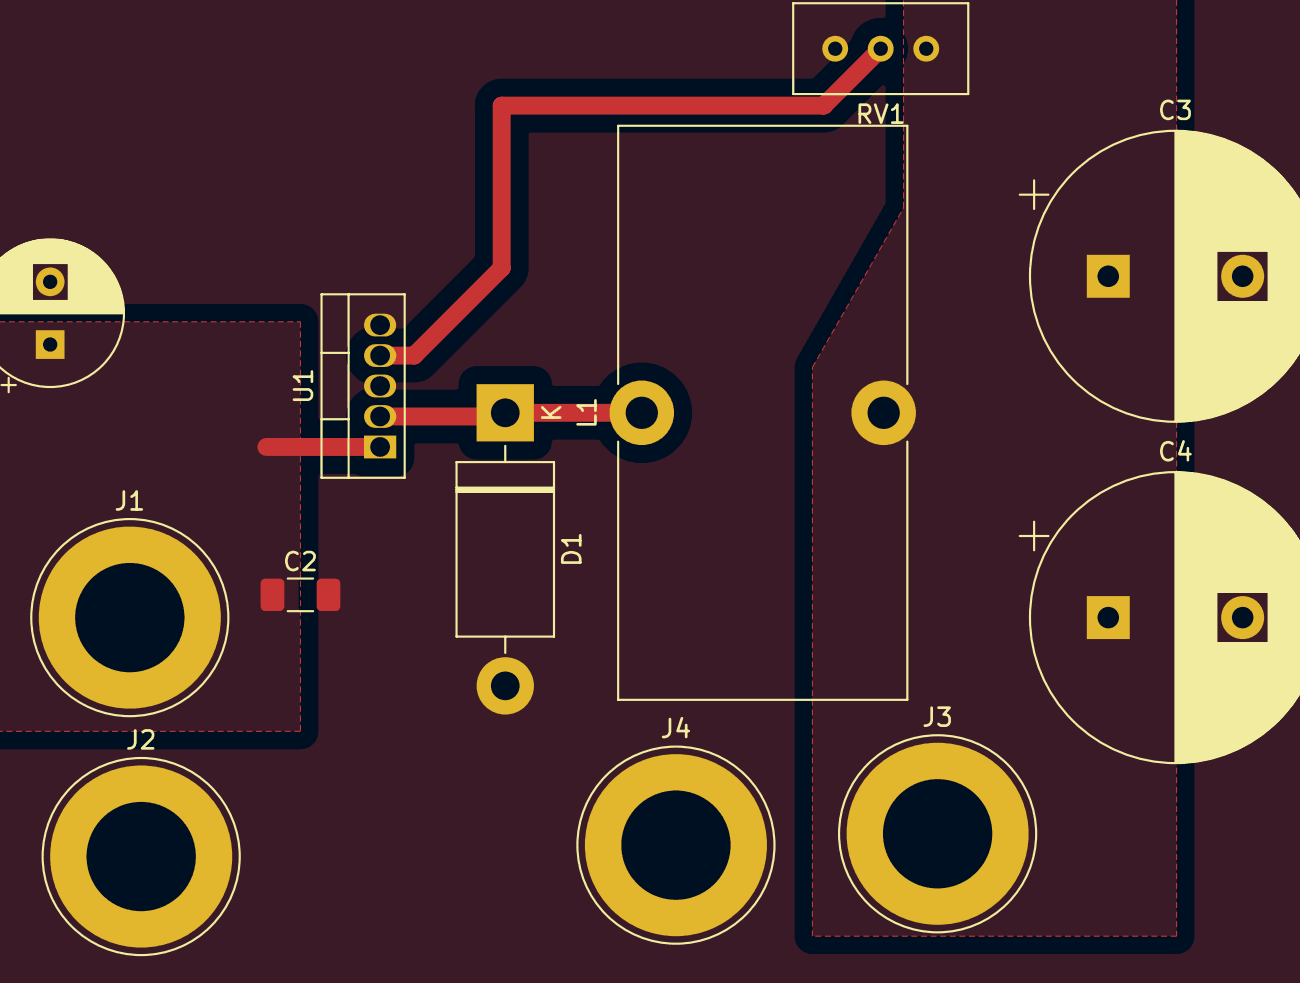
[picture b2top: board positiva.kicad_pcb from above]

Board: 2 copper layers, 12 parts (0 on the bottom side), 5 nets.

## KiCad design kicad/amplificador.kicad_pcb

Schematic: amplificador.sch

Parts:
C1: 10u; C_Disc_D10.0mm_W2.5mm_P5.00mm
C2, C4: 47u; CP_Elec_3x5.3
C3: 1000u; CP_Radial_D7.5mm_P2.50mm
C5: 100p; CP_Elec_3x5.3
C6: 22n; CP_Elec_3x5.3
C7, C8: 1u; CP_Radial_D5.0mm_P2.00mm
D3, D4: 1N4148; D_DO-35_SOD27_P7.62mm_Horizontal
D5, D6: 1N5822; D_DO-201AD_P15.24mm_Horizontal
J1, J7, J8, J14, J16, J17, J21, J22, J23, J24: Screw_Terminal_01x01; PinHeader_1x01_P2.54mm_Vertical
J2, J3, J4, J5, J6, J9, J10, J11, J12, J13, J15, J18, J19, J20: Conn_01x01_Male; PinHeader_1x01_P2.54mm_Vertical
JP1, JP2, JP3, JP4: Jumper_NO_Small; PinHeader_1x02_P2.54mm_Vertical
Q1, Q3, Q5, Q6, Q8: MPSA92; TO-92_Inline
Q2, Q4, Q7, Q10: MPSA42; TO-92_Inline
Q9, Q11, Q13: BD135; TO-126-3_Vertical
Q12, Q14: BD136; TO-126-3_Vertical
Q15, Q16: 2SD1047; TO-3PB-3_Vertical
Q17, Q18: 2SB817; TO-3PB-3_Vertical
R1, R11: 12k; R_0805_2012Metric_Pad1.15x1.40mm_HandSolder
R2, R6, R14: 68; R_0805_2012Metric_Pad1.15x1.40mm_HandSolder
R3, R4, R5, R19, R20, R21, R22: 100; R_0805_2012Metric_Pad1.15x1.40mm_HandSolder
R7, R12, R13: 2.2k; R_0805_2012Metric_Pad1.15x1.40mm_HandSolder
R8: 470; R_0805_2012Metric_Pad1.15x1.40mm_HandSolder
R9, R10: 10k; R_0805_2012Metric_Pad1.15x1.40mm_HandSolder
R15, R18: 10; R_0805_2012Metric_Pad1.15x1.40mm_HandSolder
R16: 3.3k; R_0805_2012Metric_Pad1.15x1.40mm_HandSolder
R17: 1.2k; R_0805_2012Metric_Pad1.15x1.40mm_HandSolder
R23: 220; R_0805_2012Metric_Pad1.15x1.40mm_HandSolder
R24, R25: 0.4; R_Axial_DIN0414_L11.9mm_D4.5mm_P25.40mm_Horizontal
R26: 200; R_Box_L8.4mm_W2.5mm_P5.08mm
U1, U2: LM385D-1.2; SOIC-8_3.9x4.9mm_P1.27mm

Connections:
/+Vcc: C2.2, C4.2, C7.2, J8.1, Q6.1, Q11.2 (C), Q13.2 (C), Q15.2, R4.2, R14.2
/-Vcc: C8.1, J7.1, Q12.2 (C), Q14.2 (C), Q18.2, R2.1, R6.2, R12.2, R15.2
/Io1: J19.1, Q3.3, R3.1, R5.2
/Io2: D3.2, JP4.2, Q8.3, U1.4 (A)
/Vi: C1.2, J1.1
/Vi_buffer: C5.2, JP3.2, Q7.2
/Vi_vas: Q7.1, Q10.2, R12.1
/Via: C1.1, J15.1, Q1.2, R1.2
/Vo: J14.1, JP2.2, R24.2, R25.1
/Vo_sumador: JP3.1, Q1.3, Q2.3
/Vo_vas: C5.1, D4.1, J18.1, Q10.3, U2.8 (K)
GND: C3.2, C7.1, C8.2, J21.1, J22.1, J23.1, J24.1, JP1.2, JP4.1, Q7.3, R1.1, R10.2
unnamed: C2.1, Q3.2, R7.1
unnamed: C3.1, R8.1
unnamed: C4.1, R9.2, R10.1
unnamed: C6.1, Q9.1 (E), R20.2, R26.2, U2.4 (A)
unnamed: C6.2, Q9.2 (C), R18.2, R19.2
unnamed: D3.1, Q11.3 (B)
unnamed: D4.2, Q12.3 (B)
unnamed: D5.1 (K), J16.1
unnamed: D5.2 (A), Q17.2, Q18.3, R22.1
unnamed: D6.1 (K), Q15.3, Q16.2, R21.2
unnamed: D6.2 (A), J17.1
unnamed: J2.1, Q1.1, R3.2
unnamed: J3.1, Q2.1, R2.2
unnamed: J4.1, Q3.1, R4.1
unnamed: J5.1, Q5.1, R5.1
unnamed: J6.1, Q4.1, R6.1
unnamed: J9.1, Q8.1, R13.1, R14.1
unnamed: J10.1, Q13.3 (B), R19.1
unnamed: J11.1, Q14.3 (B), R20.1
unnamed: J12.1, Q13.1 (E), Q16.1, R23.1
unnamed: J13.1, Q14.1 (E), Q17.1, R23.2
unnamed: J20.1, Q5.2, R8.2, R11.2
unnamed: JP1.1, JP2.1, R11.1
unnamed: Q2.2, Q4.2, Q4.3, Q5.3
unnamed: Q6.2, R13.2
unnamed: Q6.3, Q8.2, R7.2, R9.1
unnamed: Q9.3 (B), R16.2, R17.1
unnamed: Q10.1, R15.1
unnamed: Q11.1 (E), Q15.1, R21.1
unnamed: Q12.1 (E), Q18.1, R22.2
unnamed: Q16.3, R24.1
unnamed: Q17.3, R25.2
unnamed: R16.1, R18.1, U1.8 (K)
unnamed: R17.2, R26.1

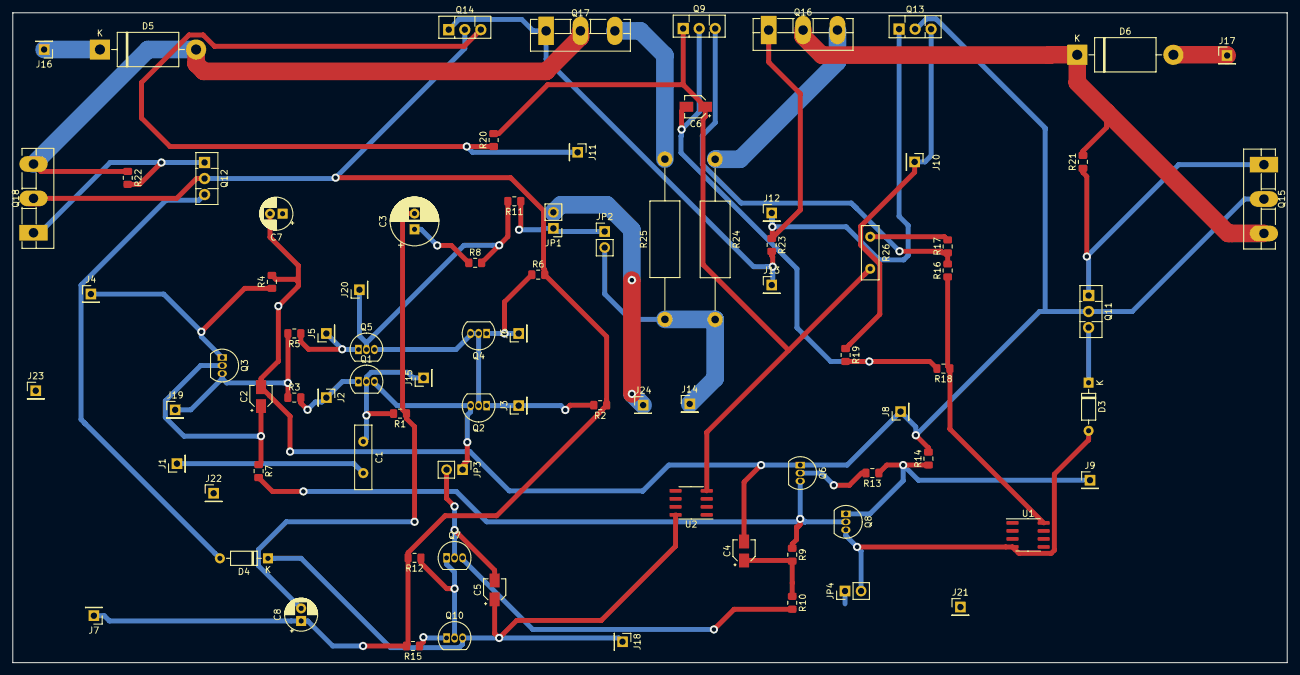
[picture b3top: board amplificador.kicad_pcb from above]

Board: 2 copper layers, 202.0 x 103.0 mm, 86 parts (0 on the bottom side), 46 nets.

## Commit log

2019-05-20 actualización del readme
2019-05-26 se agregan las especificaciones y el calendario
2019-05-31 agregamos las primeras simulaciones
2019-06-04 se actualiza el circuito total al realimentado con el sumador pero sin el seguidor de salida, queda ajustar para que de excursion simetrica
2019-06-04 actualizamos el circuito total
2019-06-05 se incluyo la fuente de corriente del douglas self en el circuito total, se elimino la realimentacion de la fte espejo del sumador y se incremento la del par diferencial, amplfifica bien sin recorte 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
2019-06-06 se agrega etapa buffer a la baja potencia
2019-06-06 agregamos analisis de compensacion, lista de materiales
2019-06-07 cambios buffer
2019-06-08 la etapa sumador y vas ya cumple las especificaciones
2019-06-10 simulacion de etapa de salida, falta reemplazar las fuentes de polarizacion
2019-06-10 fuente de salida con polarización, tiene 4 de continua a la salida, recorta
2019-06-11 se agrega la etapa de salida, polarizada y con generadores, y el circuito total. el de salida con generadores da bien salvo por una atenuacion, tiene thd de 0.7, el que esta polarizado da continua a 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
2019-06-17 circuito total con transistores de potencia a la salida y se reemplazan los zener por diodos comunes (menos caida)
2019-06-17 agregamos los archivos kicad
2019-06-17 esquematico de kicad completo, faltan las fuentes interiores de la etapa de salida nada mas
2019-06-18 Seleccionado de footprints para resistores smd
2019-06-20 Inicio del ruteo
2019-06-20 Realimentación de simulación corregida.
    Estaba conectada a la salida del VAS.
2019-06-20 agregamos las datasheets de los bc557 y bc547
2019-06-21 cambiamos las R de realimentacion por valores comerciales, la de la fte de corriente, las de emisor de la carga activa, cargamos los modelos de varios transistores de potencia
2019-06-21 pcb Kicad actualizado
2019-06-23 Primer ruteo
2019-06-23 simulacion cumpliendo especificaciones, usa todos los transistores del douglas self, agregamos datasheets y borramos modelos viejos que no se usaban
2019-06-23 arreglamos la simulacion que no se habia mergeado
2019-06-24 actualizamos lista de materiales para reconstruccion del amplificador
2019-06-26 Actualización del pcb
    Se acercaró el multiplicador de vbe a los transistores de potencia por acoplamiento térmico. Se dejó lugar para montarlos sobre un disipador.
2019-06-27 modificamos el valor del capacitor de acople y mandamos el capacitor de 1000u a V- en vez de tierra, actualizamos todos los circuitos para que tengan la realimentacion correcta y consistente
2019-06-27 cambios al pcb
2019-06-28 Ruteo del esquemático modificado
    Capacitor a -30V, encapsulados finales, capacitor de entrada de poliéster.
2019-06-28 viaje en el tiempo... el commit anterior esta roto
2019-06-29 Final de clase viernes 28 de junio
2019-07-02 carpeta kicad con esquematico con todos los encapsulados correctos, jumpers, pines de alimentacion y medicon. pcb a medio hacer
2019-07-02 cambios en los jumpers, ruteo avanzado
2019-07-02 actualizamos lista de materiales a la final, agregamos recordatorio de capa de bypass en las notas de kicad, reemplazamos el mpsa del multiplicador de vbe por un mje
2019-07-03 agregamos hojas de datos, cambiamos el esquematico un poco (footprints, sacamos algunos pines, agregamos capas de filtrado), el pcb esta dispuesto de la misma forma que el esquematico, queda optimiza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
2019-07-03 intento de optimización de pcb: seguramente haya que volver a la versión anterior y tirar una via para la realimentación...
2019-07-03 How many vias are too many vias?
2019-07-05 PCB DRC actualizado
2019-07-08 PCB versión 1.0
    Planos de alimentación, ancho de pistas y nuevos pines GND.
2019-07-13 Planos de masa separados por etapas
2019-07-16 agregamos simulaciones de ri y ro para el circuito total
2019-07-16 reemplazamos el q del mult del vbe x un mje, agregamos nombres a las nets e indicamos cuales son de potencia
2019-07-27 Se cambio el footprint del multiplicador de vbe en el pcb
2019-08-05 configurado con un clearance de 0.32 mm
2019-09-01 DRC arreglo - separación pista pad
    Problema a resolver: los transistores Q1 a Q10 (MPSA) tienen sus pad muy cercanos entre sí y no cumplen las reglas del LCI. ¿Hay que cambiar de transistores?
2019-09-01 Planos de masa agregados
2019-09-17 actualizamos lista de materiales y algunos valores del circuito que estaban mal
2019-10-29 el jumper JP4 estaba mal, tenía que ir a tierra, se actualizó el esquemático y el pcb. En el pcb se saco una via
2019-10-29 cambiamos resistencia de 200 por una de 220
2019-11-19 actualizamos la simulación del diferencial solo
2019-12-19 agregamos los valores que se deberían medir sobre la simulación del punto de operación
2019-12-20 primeras mediciones del día
2019-12-20 corregimos la conexió que faltaba en la fuente de corriente en el proyecto de kicad
2019-12-20 agregamos más anotaciones a la simulación del punto de operación
2019-12-20 agregamos los resultados de las mediciones realizadas
2020-02-03 Etapa diferencial funcionando en PCB
2020-02-04 Etapa VAS bien polarizada.
2020-02-06 Fallo en las mediciones de polarización aunque no se realizaron modificaciones al circuito diferencial-VAS
2020-02-10 trabajo del 10/02
2020-02-11 Cambio de potenciómetro y capacitor de 1uF entre VCC y GND
2020-02-13 Se soldó por primera vez la etapa de potencia. Diferencial+VAS funcionando.
2020-02-14 datasheets con resistencia térmica
2020-02-14 agrego douglas self y diapos de disipadores
2020-02-17 Se terminó de soldar la etapa de potencia. Faltan agregar los disipadores.
2020-02-23 cambiamos capa de compensación de 100p a 470p
2020-02-29 trabajo del 29/02
2020-03-05 Commits viejos realizados desde PC del laboratorio y enviados por mail.
2020-03-06 Sin avances significativos
2020-03-09 Mediciones 06/03/2020. Amplificando
2020-03-10 Pruebas realizadas con carga.
2020-03-11 Falla en la polarización del circuito.
2020-03-12 Arreglo de las pistas de tierra. Circuito sin carga en funcionamiento.
    Revisar transitorio al conectar carga.
2020-03-15 trabajo del 13/03
2020-03-17 trabajo del 16/03
2020-10-23 fuente de switching
2020-11-10 varias cosas switching
2020-11-13 docs
2021-01-04 rm backup kicad files
2021-01-04 rm cache files
2021-02-03 layout de fuente switching positiva
2021-02-15 layout inicial fuente negativa
2021-02-16 varias cosas, layouts de fuentes terminados, calculo de componentes completo
2021-02-19 last minute commit
2021-03-19 simulaciones para informe
2021-03-21 simulaciones para informe final

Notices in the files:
parts and their libraries:
Copyright 2016 Accelerated Designs. All rights reserved.
